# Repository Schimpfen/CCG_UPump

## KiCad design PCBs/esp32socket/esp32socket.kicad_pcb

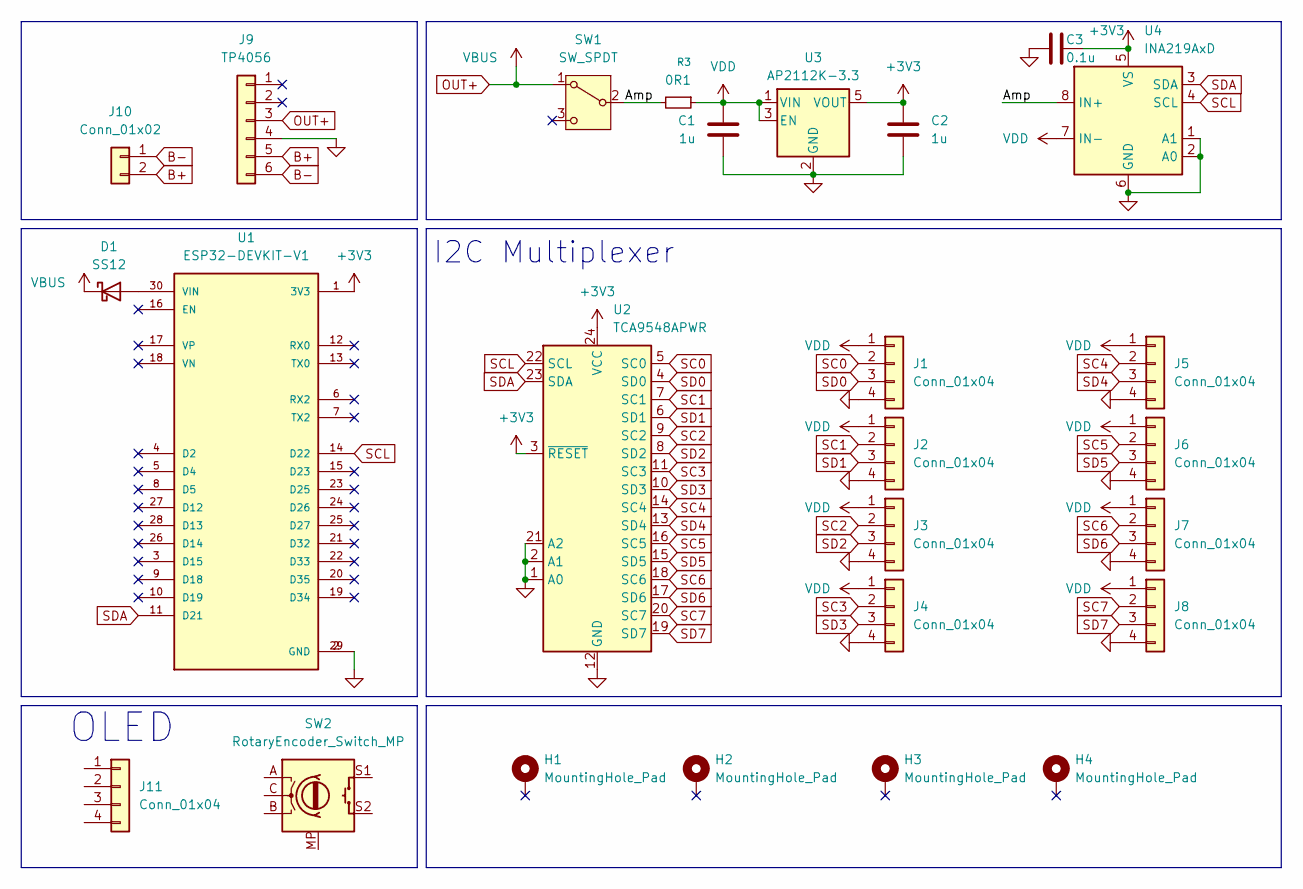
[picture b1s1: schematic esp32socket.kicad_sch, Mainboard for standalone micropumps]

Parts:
C1, C2: 1u; C_0805_2012Metric
C3: 0.1u; C_0805_2012Metric
D1: SS12; D_SMA
H1, H2, H3, H4: MountingHole_Pad; MountingHole_3.2mm_M3_DIN965_Pad
J1, J2, J3, J4, J5, J6, J7, J8: Conn_01x04; JST_XH_B4B-XH-A_1x04_P2.50mm_Vertical
J9: TP4056; TP4056-18650
J10: Conn_01x02; JST_PH_S2B-PH-K_1x02_P2.00mm_Horizontal
J11: Conn_01x04; PinHeader_1x04_P2.54mm_Vertical
R3: 0R1; R_1210_3225Metric
SW1: SW_SPDT; SW_Slide_SPDT_Straight_CK_OS102011MS2Q
SW2: RotaryEncoder_Switch_MP; RotaryEncoder_Alps_EC12E-Switch_Vertical_H20mm_CircularMoun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
U1: ESP32-DEVKIT-V1; MODULE_ESP32_DEVKIT_V1; PARTREV N/A
U2: TCA9548APWR; TCA9548A
U3: AP2112K-3.3; SOT-23-5
U4: INA219AxD; SOIC-8_3.9x4.9mm_P1.27mm

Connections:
+3V3: C2.2, C3.2, U1.1 (3V3), U2.3 (~RESET), U2.24 (VCC), U3.5 (VOUT), U4.5 (VS)
/Amp: R3.2, SW1.2 (B), U4.8 (IN+)
B+: J9.5, J10.2
B-: J9.6, J10.1
GND: C1.1, C2.1, C3.1, J1.4, J2.4, J3.4, J4.4, J5.4, J6.4, J7.4, J8.4, J9.4, U1.2 (GND), U1.29 (GND), U2.1 (A0), U2.2 (A1), U2.12 (GND), U2.21 (A2), U3.2 (GND), U4.1 (A1), U4.2 (A0), U4.6 (GND)
unnamed: D1.2 (A), U1.30 (VIN)
OUT+: D1.1 (K), J9.3, SW1.1 (A)
SC0: J1.2, U2.5 (SC0)
SC1: J2.2, U2.7 (SC1)
SC2: J3.2, U2.9 (SC2)
SC3: J4.2, U2.11 (SC3)
SC4: J5.2, U2.14 (SC4)
SC5: J6.2, U2.16 (SC5)
SC6: J7.2, U2.18 (SC6)
SC7: J8.2, U2.20 (SC7)
SCL: U1.14 (D22), U2.22 (SCL), U4.4 (SCL)
SD0: J1.3, U2.4 (SD0)
SD1: J2.3, U2.6 (SD1)
SD2: J3.3, U2.8 (SD2)
SD3: J4.3, U2.10 (SD3)
SD4: J5.3, U2.13 (SD4)
SD5: J6.3, U2.15 (SD5)
SD6: J7.3, U2.17 (SD6)
SD7: J8.3, U2.19 (SD7)
SDA: U1.11 (D21), U2.23 (SDA), U4.3 (SDA)
VDD: C1.2, J1.1, J2.1, J3.1, J4.1, J5.1, J6.1, J7.1, J8.1, R3.1, U3.1 (VIN), U3.3 (EN), U4.7 (IN-)

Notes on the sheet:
OLED
I2C Multiplexer

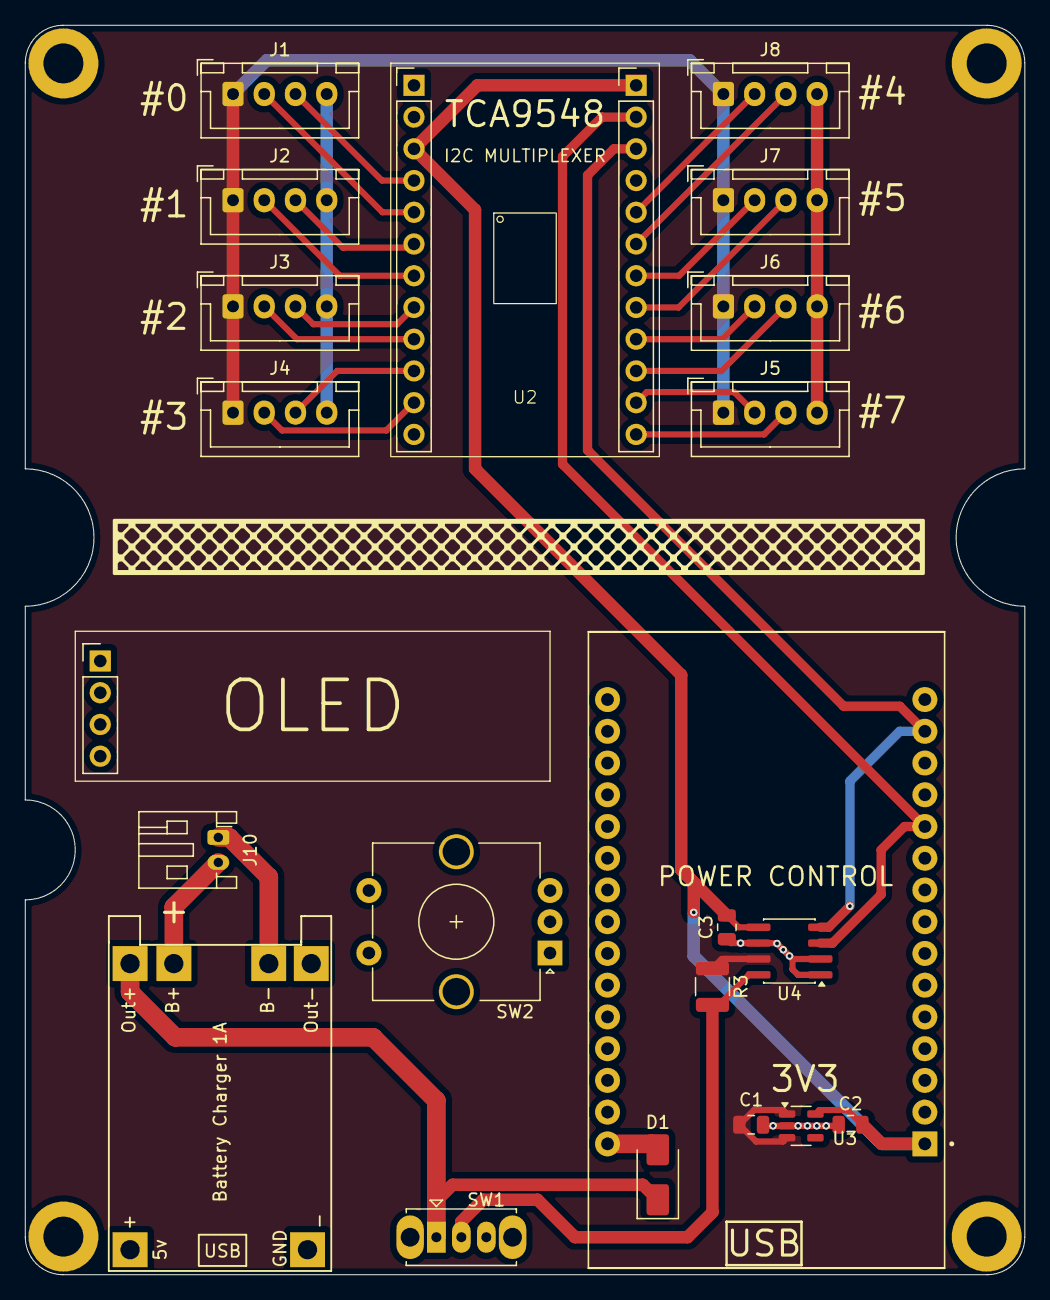
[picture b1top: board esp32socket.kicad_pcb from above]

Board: 2 copper layers, 80.0 x 100.0 mm, 26 parts (0 on the bottom side), 26 nets.

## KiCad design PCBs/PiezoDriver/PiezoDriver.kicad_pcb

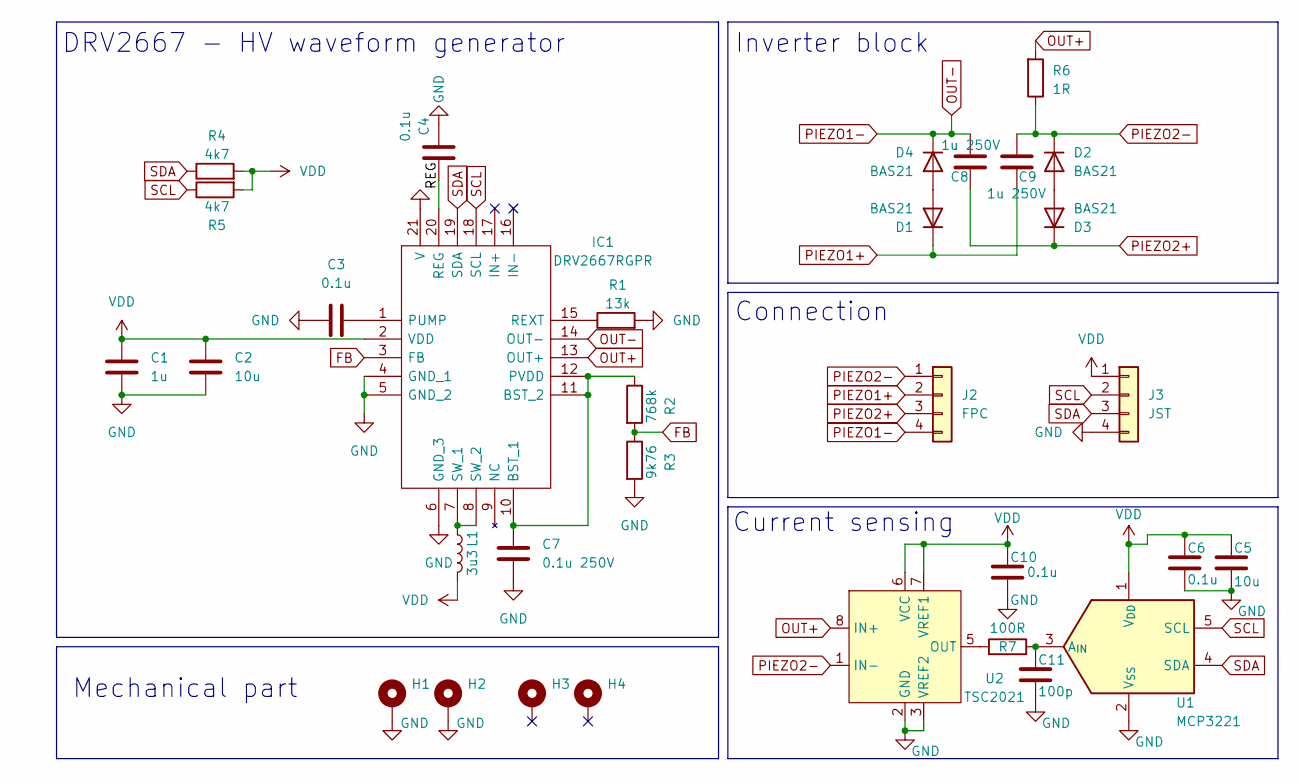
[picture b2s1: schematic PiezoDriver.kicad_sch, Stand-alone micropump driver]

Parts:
C1: 1u; C_0805_2012Metric
C2, C5: 10u; C_0805_2012Metric
C3, C4, C6, C10: 0.1u; C_0805_2012Metric
C7: 0.1u 250V; C_1206_3216Metric
C8, C9: 1u 250V; C_1812_4532Metric
C11: 100p; C_0805_2012Metric
D1, D2, D3, D4: BAS21; SOT-23
H1, H2, H3, H4: MountingHole_Pad; MountingHole_3.2mm_M3_DIN965_Pad
IC1: DRV2667RGPR; RGP20_2P7X2P7; Mouser Part Number 595-DRV2667RGPR
J2: FPC; FPC_4p_THT
J3: JST; JST_XH_S4B-XH-A-1_1x04_P2.50mm_Horizontal
L1: 3u3; L_Ferrocore_DLG-0403
R1: 13k; R_0805_2012Metric
R2: 768k; R_0805_2012Metric
R3: 9k76; R_0805_2012Metric
R4, R5: 4k7; R_0805_2012Metric
R6: 1R; R_0805_2012Metric
R7: 100R; R_0805_2012Metric
U1: MCP3221; SOT-23-5
U2: TSC2021; SO-8_3.9x4.9mm_P1.27mm

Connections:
/REG: C4.1, IC1.20 (REG)
FB: IC1.3 (FB), R2.2, R3.1
GND: C1.2, C2.2, C3.1, C4.2, C5.2, C6.1, C7.1, C10.1, C11.1, H1.1, H2.1, IC1.4 (GND_1), IC1.5 (GND_2), IC1.6 (GND_3), IC1.21 (V), J3.4, R1.2, R3.2, U1.2 (V_{SS}), U2.2 (GND), U2.3 (VREF2)
unnamed: D1.1 (A), D4.1 (A)
unnamed: D2.1 (A), D3.1 (A)
unnamed: C7.2, IC1.10 (BST_1), IC1.11 (BST_2), IC1.12 (PVDD), R2.1
unnamed: C3.2, IC1.1 (PUMP)
unnamed: IC1.15 (REXT), R1.1
unnamed: IC1.7 (SW_1), IC1.8 (SW_2), L1.1
unnamed: C11.2, R7.1, U1.3 (A_{IN})
unnamed: R7.2, U2.5 (OUT)
OUT+: IC1.13 (OUT+), R6.2, U2.8 (IN+)
OUT-: C8.1, D4.3 (K), IC1.14 (OUT-), J2.4
PIEZO1+: C9.2, D1.3 (K), J2.2
PIEZO2+: C8.2, D3.3 (K), J2.3
PIEZO2-: C9.1, D2.3 (K), J2.1, R6.1, U2.1 (IN-)
SCL: IC1.18 (SCL), J3.2, R5.1, U1.5 (SCL)
SDA: IC1.19 (SDA), J3.3, R4.1, U1.4 (SDA)
VDD: C1.1, C2.1, C5.1, C6.2, C10.2, IC1.2 (VDD), J3.1, L1.2, R4.2, R5.2, U1.1 (V_{DD}), U2.6 (VCC), U2.7 (VREF1)

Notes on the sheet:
Inverter block
Current sensing
Mechanical part
Connection
DRV2667 - HV waveform generator

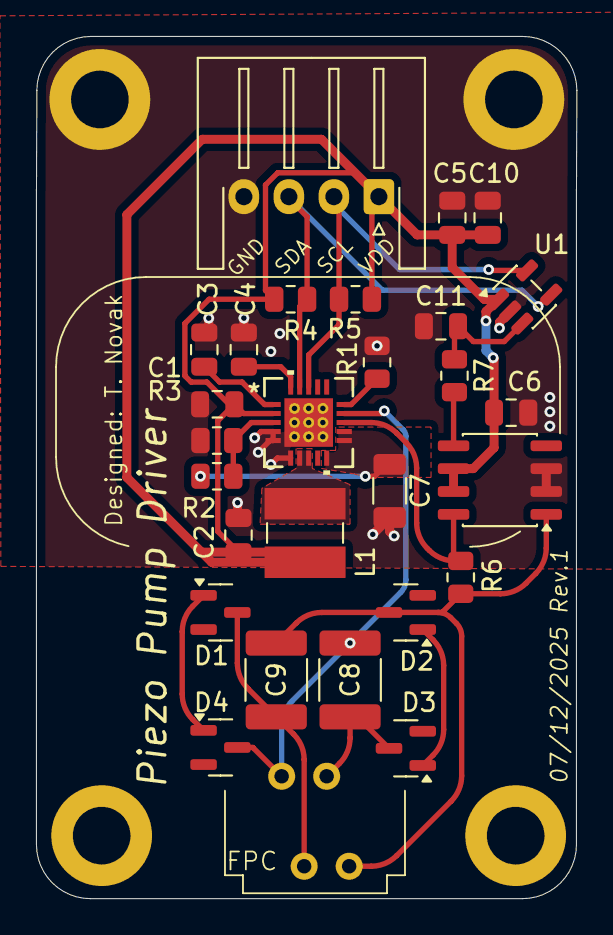
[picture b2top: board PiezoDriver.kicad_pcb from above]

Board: 2 copper layers, 30.0 x 47.9 mm, 32 parts (0 on the bottom side), 19 nets.

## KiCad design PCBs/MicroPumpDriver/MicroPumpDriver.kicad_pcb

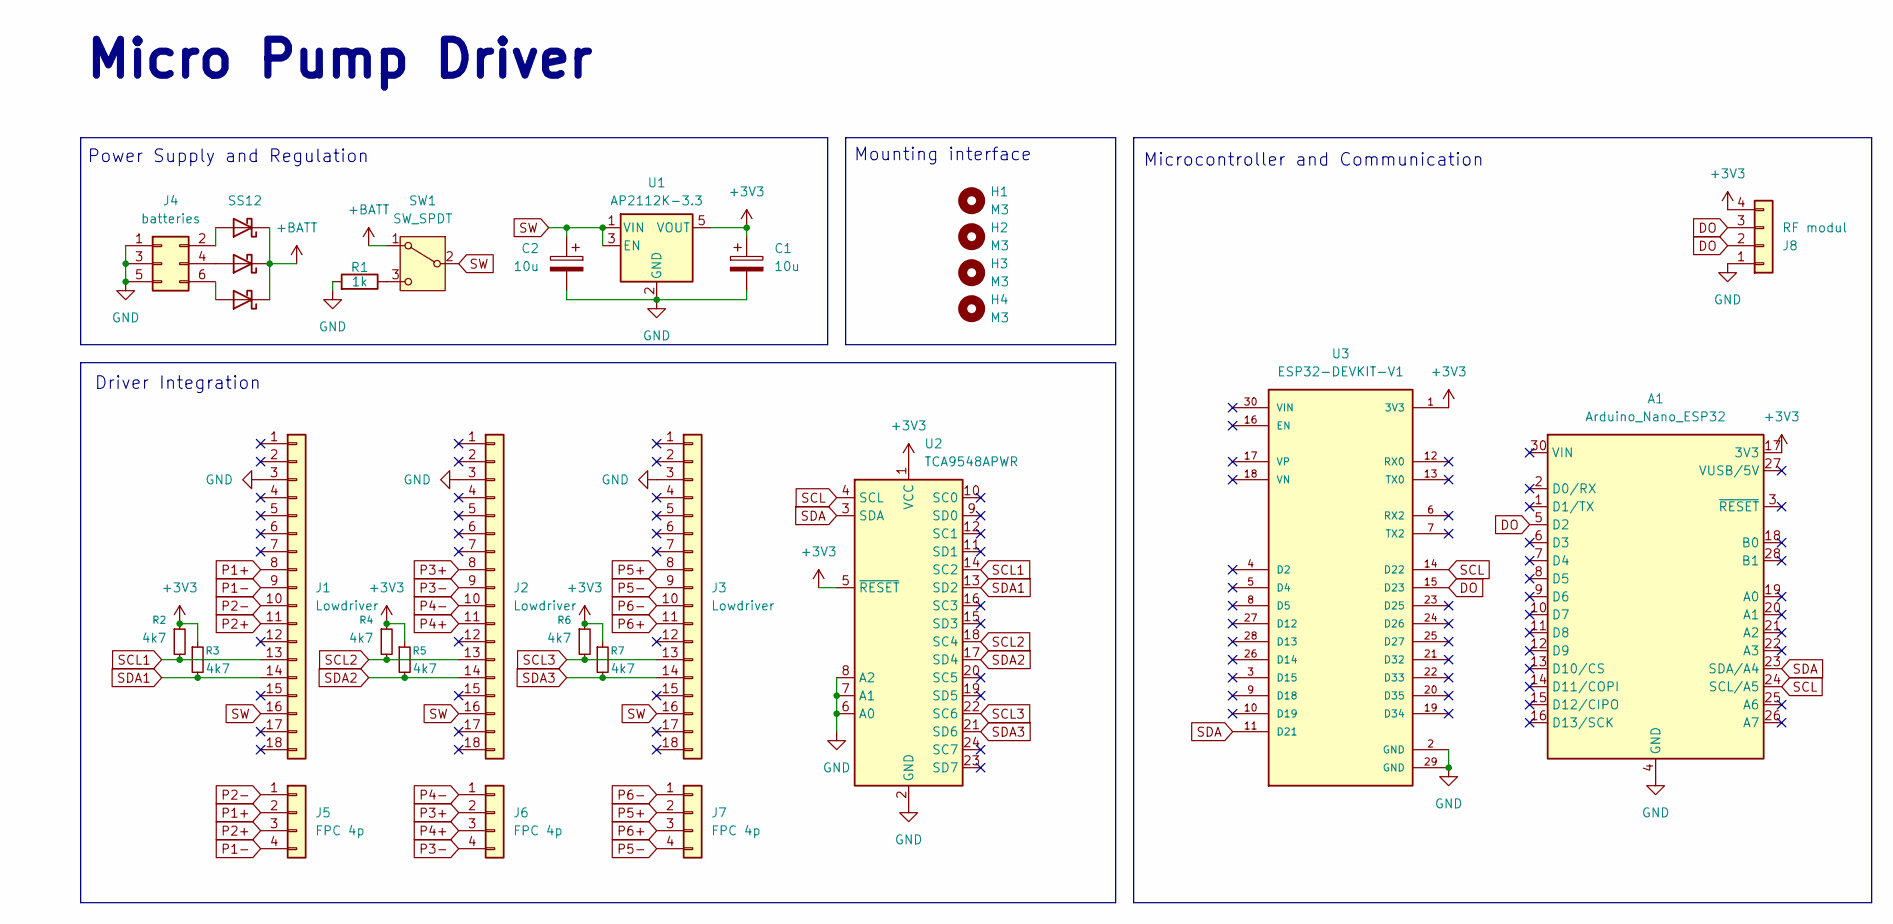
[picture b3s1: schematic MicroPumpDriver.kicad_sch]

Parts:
A1: Arduino_Nano_ESP32; Arduino_Nano
C1, C2: 10u; CP_Elec_4x5.8
D1, D2, D3: SS12; D_SMA-SMB_Universal_Handsoldering
H1, H2, H3, H4: M3; MountingHole_3.2mm_M3
J1, J2, J3: Lowdriver; DIP-18_W7.62mm_Socket
J4: batteries; PinHeader_2x03_P2.54mm_Vertical
J5, J6, J7: FPC 4p; FPC_4p_THT
J8: RF modul; PinSocket_1x04_P2.54mm_Vertical
R1: 1k; R_Axial_DIN0207_L6.3mm_D2.5mm_P10.16mm_Horizontal
R2, R3, R4, R5, R6, R7: 4k7; R_Axial_DIN0207_L6.3mm_D2.5mm_P7.62mm_Horizontal
SW1: SW_SPDT; JST_XH_S3B-XH-A_1x03_P2.50mm_Horizontal
U1: AP2112K-3.3; SOT-23-5
U2: TCA9548APWR; TCA9548A
U3: ESP32-DEVKIT-V1; MODULE_ESP32_DEVKIT_V1; PARTREV N/A

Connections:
+3V3: A1.17 (3V3), C1.1, J8.4, R2.1, R3.1, R4.1, R5.1, R6.1, R7.1, U1.5 (VOUT), U2.1 (VCC), U2.5 (~RESET), U3.1 (3V3)
+BATT: D1.1 (K), D2.1 (K), D3.1 (K), SW1.1 (A)
DO: A1.5 (D2), J8.2, J8.3, U3.15 (D23)
GND: A1.4 (GND), A1.29 (GND), C1.2, C2.2, J1.3, J2.3, J3.3, J4.1, J4.3, J4.5, J8.1, R1.2, U1.2 (GND), U2.2 (GND), U2.6 (A0), U2.7 (A1), U2.8 (A2), U3.2 (GND), U3.29 (GND)
unnamed: D1.2 (A), J4.2
unnamed: D2.2 (A), J4.4
unnamed: D3.2 (A), J4.6
unnamed: R1.1, SW1.3 (C)
P1+: J1.8, J5.2
P1-: J1.9, J5.4
P2+: J1.11, J5.3
P2-: J1.10, J5.1
P3+: J2.8, J6.2
P3-: J2.9, J6.4
P4+: J2.11, J6.3
P4-: J2.10, J6.1
P5+: J3.8, J7.2
P5-: J3.9, J7.4
P6+: J3.11, J7.3
P6-: J3.10, J7.1
SCL: A1.24 (SCL/A5), U2.4 (SCL), U3.14 (D22)
SCL1: J1.13, R2.2, U2.14 (SC2)
SCL2: J2.13, R4.2, U2.18 (SC4)
SCL3: J3.13, R6.2, U2.22 (SC6)
SDA: A1.23 (SDA/A4), U2.3 (SDA), U3.11 (D21)
SDA1: J1.14, R3.2, U2.13 (SD2)
SDA2: J2.14, R5.2, U2.17 (SD4)
SDA3: J3.14, R7.2, U2.21 (SD6)
SW: C2.1, J1.16, J2.16, J3.16, SW1.2 (B), U1.1 (VIN), U1.3 (EN)

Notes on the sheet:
Power Supply and Regulation
Mounting interface
Micro Pump Driver
Microcontroller and Communication
Driver Integration

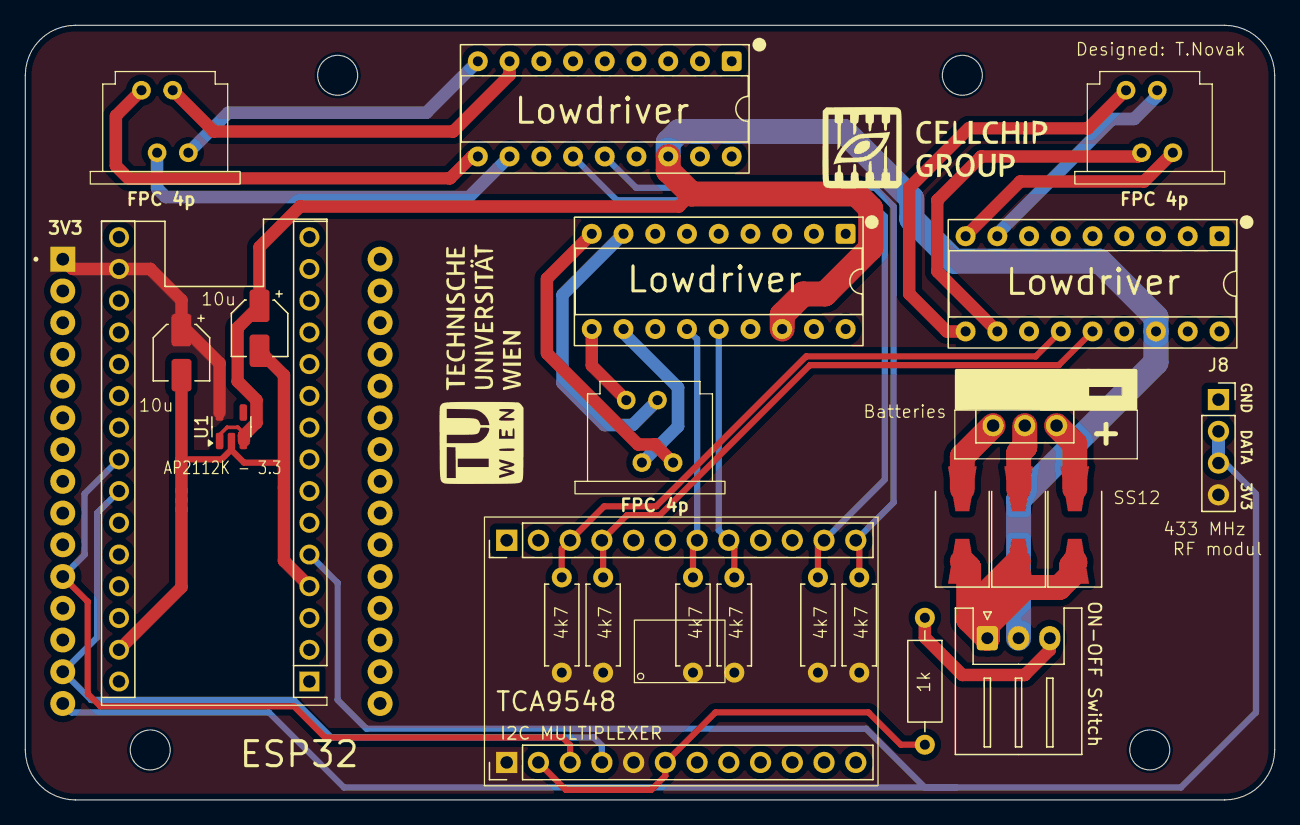
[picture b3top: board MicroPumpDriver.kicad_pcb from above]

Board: 2 copper layers, 100.0 x 62.0 mm, 29 parts (0 on the bottom side), 29 nets.

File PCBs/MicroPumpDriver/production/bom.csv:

Designator,Footprint,Quantity,Value,LCSC Part #
A1,Arduino_Nano,1,Arduino_Nano_ESP32,
"C1, C2",CP_Elec_4x5.8,2,10u,
"D1, D2, D3",D_SMA-SMB_Universal_Handsoldering,3,SS12,
"J1, J2, J3",DIP-18_W7.62mm_Socket,3,Lowdriver,
J4,PinHeader_2x03_P2.54mm_Vertical,1,batteries,
"J5, J6, J7",FPC_4p_THT,3,FPC 4p,
J8,PinSocket_1x04_P2.54mm_Vertical,1,RF modul,
R1,R_Axial_DIN0207_L6.3mm_D2.5mm_P10.16mm_Horizontal,1,1k,
"R2, R3, R4, R5, R6, R7",R_Axial_DIN0207_L6.3mm_D2.5mm_P7.62mm_Horizontal,6,4k7,
SW1,JST_XH_S3B-XH-A_1x03_P2.50mm_Horizontal,1,SW_SPDT,
U1,SOT-23-5,1,AP2112K-3.3,
U2,TCA9548A,1,TCA9548APWR,
U3,MODULE_ESP32_DEVKIT_V1,1,ESP32-DEVKIT-V1,

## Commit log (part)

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2025-12-02 found it
2025-12-02 fixesbacktofront
2025-12-09 Bachelorthesis
